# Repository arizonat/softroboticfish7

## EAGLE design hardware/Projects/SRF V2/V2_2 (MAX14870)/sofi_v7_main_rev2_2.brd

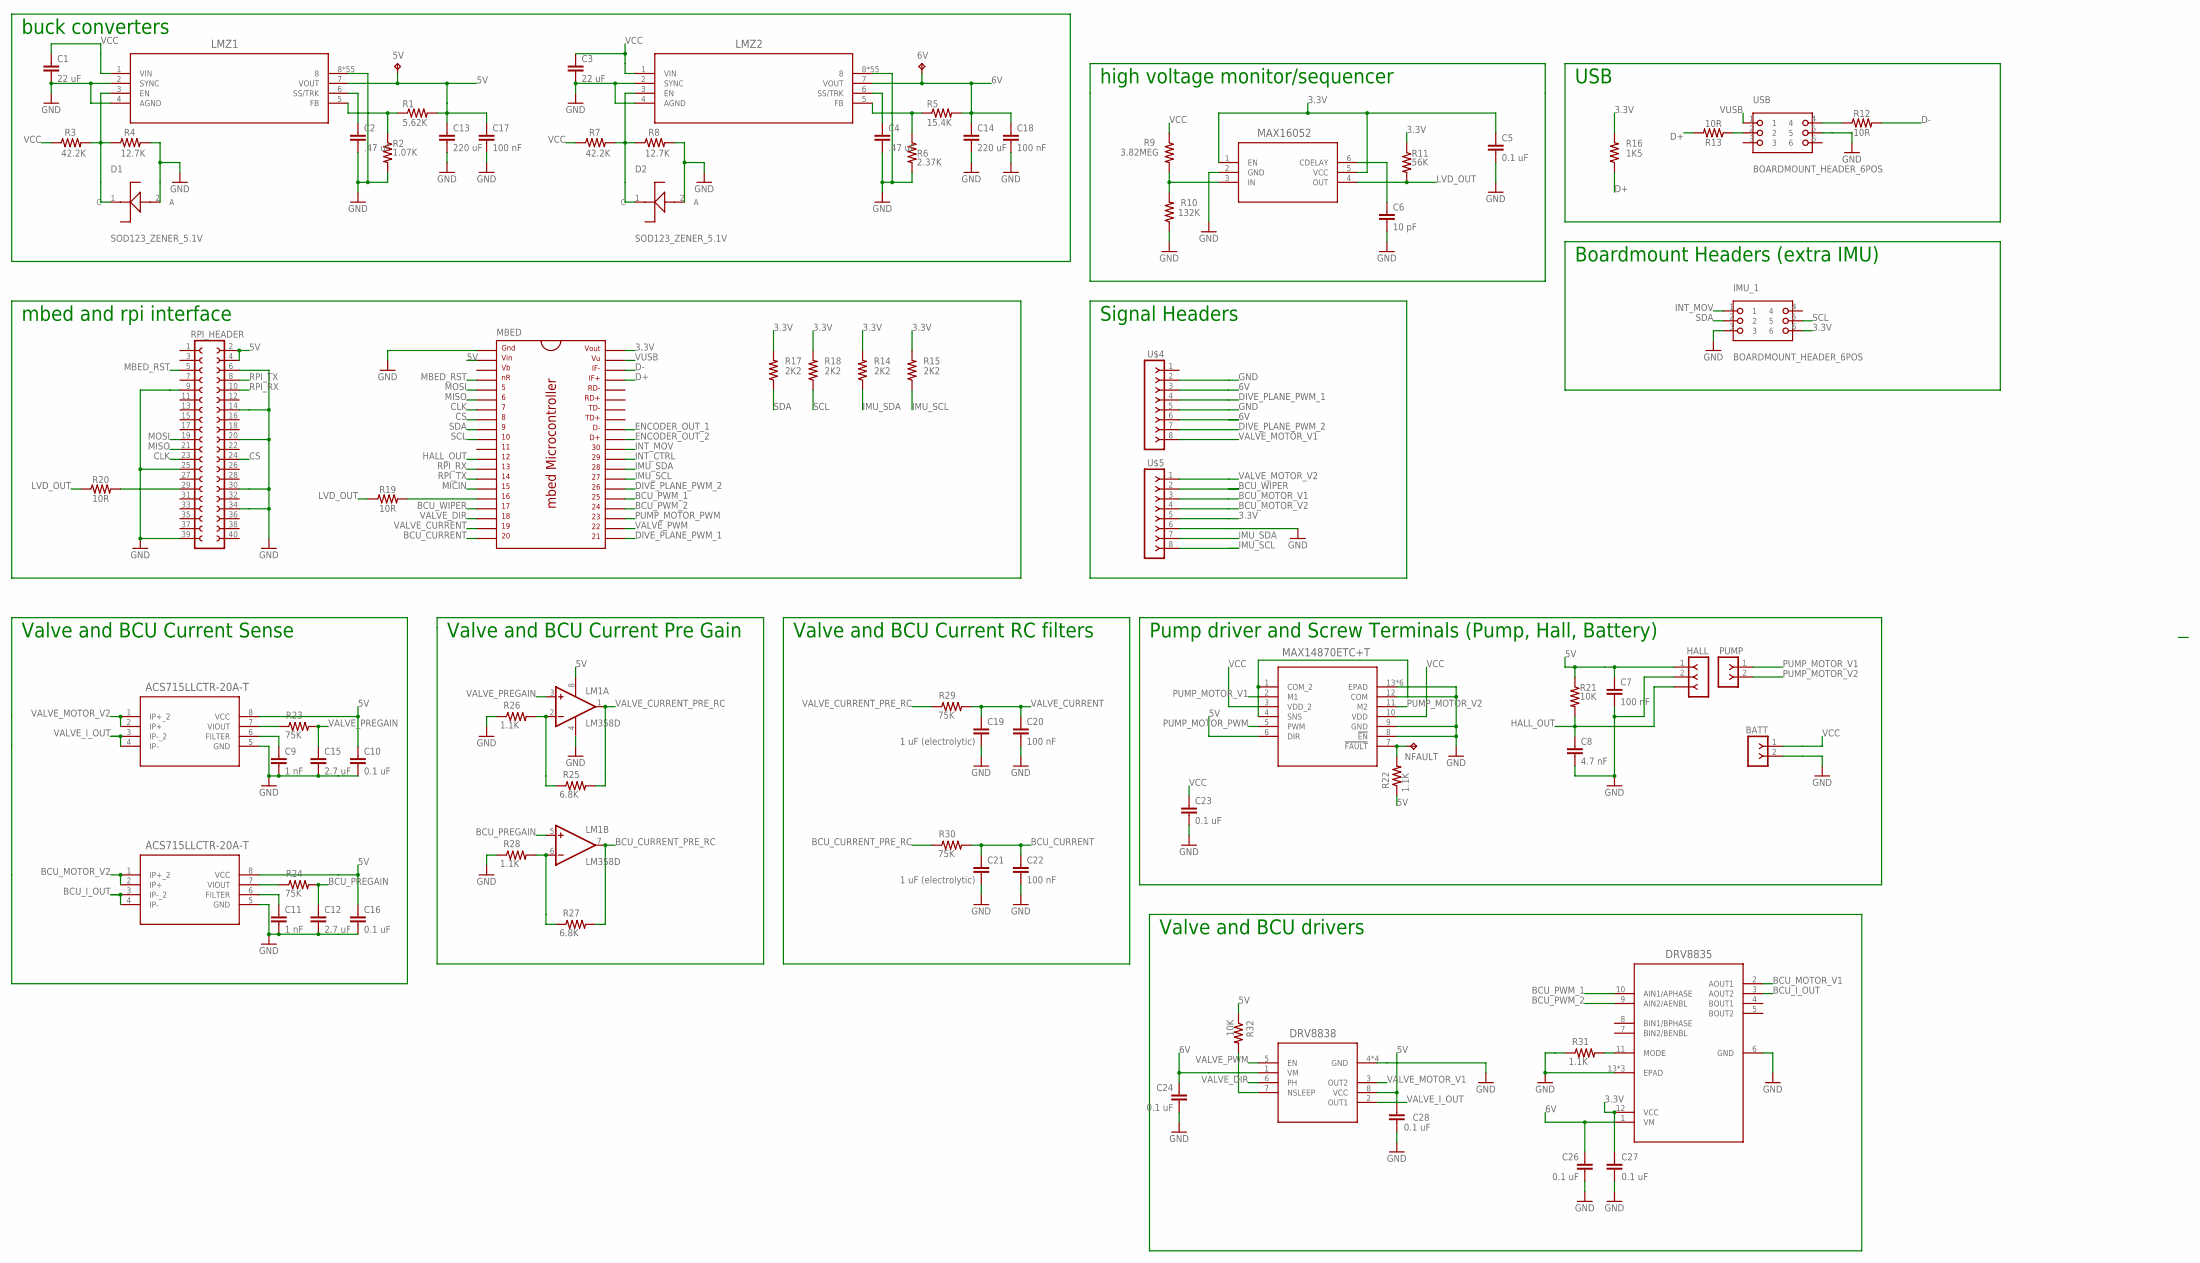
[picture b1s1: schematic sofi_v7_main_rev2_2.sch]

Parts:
5V, 6V: TPB1,27; B1,27
ACS715_BCU, ACS715_VALVE: ACS715LLCTR-20A-T; SOIC-8
BATT: 2POS_BLOCK2POS_BLOCK_NOSTANDS; 2POS_BLOCK_NOSTANDS
C1, C3: 22 uF; C0805
C2, C4: .47 uF; C0805
C5, C23: 0.1 uF; C0805
C6: 10 pF; C0603
C7, C17, C18, C20, C22: 100 nF; C0805
C8: 4.7 nF; C0805
C9, C11: 1 nF; C0603
C10, C16, C24, C26, C27, C28: 0.1 uF; C0603
C12, C15: 2.7 uF; C0603
C13, C14: 220 uF; C1206
C19, C21: 1 uF (electrolytic); C0603
D1, D2: SOD123_ZENER_5.1V; SOD123_ZENER
DRV8835: DRV8835DSSRDSS12_P9X2_THERMAL_EXTENDED; DSS12_P9X2_THERMAL_EXTENDED
DRV8838: DRV8838DSGTDSG8_P9X1P6_THERMAL_EXTENDED; DSG8_P9X1P6_THERMAL_EXTENDED
HALL: 3POS_TERMINAL
IMU_1: BOARDMOUNT_HEADER_6POS; BOARDMOUNT_HEADER
LM1: LM358D; SO08
LMZ1, LMZ2: LMZ23605TZE/NOPBTZA07A_THERMAL_TABBED; TZA07A_THERMAL_TABBED
MAX14870: MAX14870ETC+T; 21-0664B
MAX16052: MAX16052AUT+T; 21-0058I
MBED: MBED_MICROCONTROLLER; DIL40_0.9
NFAULT: TPB1,27; B1,27
PUMP: 2POS_BLOCK2POS_BLOCK_NOSTANDS; 2POS_BLOCK_NOSTANDS
R1: 5.62K; M0805
R2: 1.07K; M0805
R3, R7: 42.2K; M0805
R4, R8: 12.7K; M0805
R5: 15.4K; M0805
R6: 2.37K; M0805
R9: 3.82MEG; 0603
R10: 132K; 0603
R11: 56K; R0603
R12, R13, R19, R20: 10R; 0603
R14, R15, R17, R18: 2K2; 0603
R16: 1K5; 0603
R21, R32: 10K; M0805
R22, R26, R28, R31: 1.1K; M0805
R23, R24, R29, R30: 75K; M0805
R25, R27: 6.8K; M0805
RPI_HEADER: FE20-2
U$4, U$5: 8POS_TERMINAL
USB: BOARDMOUNT_HEADER_6POS; BOARDMOUNT_HEADER

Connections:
3.3V: C5.1, C27.1, DRV8835.12 (VCC), IMU_1.6, MAX16052.1 (EN), MAX16052.5 (VCC), MBED.40, R11.1, R14.2, R15.2, R16.2, R17.2, R18.2, U$5.5
5V: 5V.TP, ACS715_BCU.8 (VCC), ACS715_VALVE.8 (VCC), C7.1, C10.1, C13.1, C16.1, C17.1, C28.1, DRV8838.8 (VCC), HALL.1, LM1.8 (V+), LMZ1.7 (VOUT), MAX14870.6 (DIR), MBED.2, R1.2, R21.1, R22.1, R32.1, RPI_HEADER.2, RPI_HEADER.4
6V: 6V.TP, C14.1, C18.1, C24.1, C26.1, DRV8835.1 (VM), DRV8838.1 (VM), LMZ2.7 (VOUT), R5.2, U$4.3, U$4.6
BCU_CURRENT: C21.1, C22.1, MBED.20, R30.2
BCU_CURRENT_PRE_RC: LM1.7 (OUT), R27.2, R30.1
BCU_I_OUT: ACS715_BCU.3 (IP-_2), ACS715_BCU.4 (IP-), DRV8835.3 (AOUT2)
BCU_MOTOR_V1: DRV8835.2 (AOUT1), U$5.3
BCU_MOTOR_V2: ACS715_BCU.1 (IP+_2), ACS715_BCU.2 (IP+), U$5.4
BCU_PREGAIN: C12.1, LM1.5 (+IN), R24.2
BCU_PWM_1: DRV8835.10 (AIN1/APHASE), MBED.25
BCU_PWM_2: DRV8835.9 (AIN2/AENBL), MBED.24
BCU_WIPER: MBED.17, U$5.2
CLK: MBED.7, RPI_HEADER.23
CS: MBED.8, RPI_HEADER.24
D+: MBED.37, R13.2, R16.1
D-: MBED.38, R12.2
DIVE_PLANE_PWM_1: MBED.21, U$4.4
DIVE_PLANE_PWM_2: MBED.26, U$4.7
ENCODER_OUT_1: MBED.32
ENCODER_OUT_2: MBED.31
GND: ACS715_BCU.5 (GND), ACS715_VALVE.5 (GND), BATT.2, C1.2, C2.2, C3.2, C4.2, C5.2, C6.2, C7.2, C8.2, C9.2, C10.2, C11.2, C12.2, C13.2, C14.2, C15.2, C16.2, C17.2, C18.2, C19.2, C20.2, C21.2, C22.2, C23.2, C24.2, C26.2, C27.2, C28.2, D1.2 (A), D2.2 (A), DRV8835.6 (GND), DRV8835.13 (EPAD), DRV8835.P$1 (EPAD), DRV8835.P$2 (EPAD), DRV8838.4 (GND), DRV8838.9 (GND), DRV8838.P$1 (GND), DRV8838.P$2 (GND), HALL.2, IMU_1.3, LM1.4 (V-), LMZ1.2 (SYNC), LMZ1.4 (AGND), LMZ1.8, LMZ1.P$1 (8), LMZ1.P$2 (8), LMZ1.P$3 (8), LMZ1.P$4 (8), LMZ1.P$5 (8), LMZ1.P$6 (8), LMZ1.P$7 (8), LMZ1.P$8 (8), LMZ1.P$9 (8), LMZ1.P$10 (8), LMZ1.P$11 (8), LMZ1.P$12 (8), LMZ1.P$13 (8), LMZ1.P$14 (8), LMZ1.P$15 (8), LMZ1.P$16 (8), LMZ1.P$17 (8), LMZ1.P$18 (8), LMZ1.P$19 (8), LMZ1.P$20 (8), LMZ1.P$21 (8), LMZ1.P$22 (8), LMZ1.P$23 (8), LMZ1.P$24 (8), LMZ1.P$25 (8), LMZ1.P$26 (8), LMZ1.P$27 (8), LMZ1.P$28 (8), LMZ1.P$29 (8), LMZ1.P$30 (8), LMZ1.P$31 (8), LMZ1.P$32 (8), LMZ1.P$33 (8), LMZ1.P$34 (8), LMZ1.P$35 (8), LMZ1.P$36 (8), LMZ1.P$37 (8), LMZ1.P$38 (8), LMZ1.P$39 (8), LMZ1.P$40 (8), LMZ1.P$41 (8), LMZ1.P$42 (8), LMZ1.P$43 (8), LMZ1.P$44 (8), LMZ1.P$45 (8), LMZ1.P$46 (8), LMZ1.P$47 (8), LMZ1.P$48 (8), LMZ1.P$49 (8), LMZ1.P$50 (8), LMZ1.P$51 (8), LMZ1.P$52 (8), LMZ1.P$53 (8), LMZ1.P$54 (8), LMZ2.2 (SYNC), LMZ2.4 (AGND), LMZ2.8, LMZ2.P$1 (8), LMZ2.P$2 (8), LMZ2.P$3 (8), LMZ2.P$4 (8), LMZ2.P$5 (8), LMZ2.P$6 (8), LMZ2.P$7 (8), LMZ2.P$8 (8), LMZ2.P$9 (8), LMZ2.P$10 (8), LMZ2.P$11 (8), LMZ2.P$12 (8), LMZ2.P$13 (8), LMZ2.P$14 (8), LMZ2.P$15 (8), LMZ2.P$16 (8), LMZ2.P$17 (8), LMZ2.P$18 (8), LMZ2.P$19 (8), LMZ2.P$20 (8), LMZ2.P$21 (8), LMZ2.P$22 (8), LMZ2.P$23 (8), LMZ2.P$24 (8), LMZ2.P$25 (8), LMZ2.P$26 (8), LMZ2.P$27 (8), LMZ2.P$28 (8), LMZ2.P$29 (8), LMZ2.P$30 (8), LMZ2.P$31 (8), LMZ2.P$32 (8), LMZ2.P$33 (8), LMZ2.P$34 (8), LMZ2.P$35 (8), LMZ2.P$36 (8), LMZ2.P$37 (8), LMZ2.P$38 (8), LMZ2.P$39 (8), LMZ2.P$40 (8), LMZ2.P$41 (8), LMZ2.P$42 (8), LMZ2.P$43 (8), LMZ2.P$44 (8), LMZ2.P$45 (8), LMZ2.P$46 (8), LMZ2.P$47 (8), LMZ2.P$48 (8), LMZ2.P$49 (8), LMZ2.P$50 (8), LMZ2.P$51 (8), LMZ2.P$52 (8), LMZ2.P$53 (8), LMZ2.P$54 (8), MAX14870.1 (COM_2), MAX14870.4 (SNS), MAX14870.8 (!EN), MAX14870.9 (GND), MAX14870.12 (COM), MAX14870.13 (EPAD), MAX14870.14 (EPAD), MAX14870.15 (EPAD), MAX14870.16 (EPAD), MAX14870.17 (EPAD), MAX14870.18 (EPAD), MAX16052.2 (GND), MBED.1, R2.2, R4.2, R6.2, R8.2, R10.1, R26.1, R28.1, R31.1, RPI_HEADER.6, RPI_HEADER.9, RPI_HEADER.14, RPI_HEADER.20, RPI_HEADER.25, RPI_HEADER.30, RPI_HEADER.34, RPI_HEADER.39, U$4.2, U$4.5, U$5.6, USB.5
HALL_OUT: C8.1, HALL.3, MBED.12, R21.2
IMU_SCL: MBED.27, R15.1, U$5.8
IMU_SDA: MBED.28, R14.1, U$5.7
INT_CTRL: MBED.29
INT_MOV: IMU_1.1, MBED.30
LVD_OUT: MAX16052.4 (OUT), R11.2, R19.1, R20.1
MBED_RST: MBED.4, RPI_HEADER.5
MICIN: MBED.15
MISO: MBED.6, RPI_HEADER.21
MOSI: MBED.5, RPI_HEADER.19
unnamed: R20.2, RPI_HEADER.29
unnamed: MAX14870.7 (!FAULT), NFAULT.TP, R22.2
unnamed: LMZ1.5 (FB), R1.1, R2.1
unnamed: MAX16052.3 (IN), R9.2, R10.2
unnamed: D1.1 (C), LMZ1.3 (EN), R3.2, R4.1
unnamed: C4.1, LMZ2.6 (SS/TRK)
unnamed: LMZ2.5 (FB), R5.1, R6.1
unnamed: C2.1, LMZ1.6 (SS/TRK)
unnamed: C6.1, MAX16052.6 (CDELAY)
unnamed: D2.1 (C), LMZ2.3 (EN), R7.2, R8.1
unnamed: ACS715_VALVE.7 (VIOUT), R23.1
unnamed: ACS715_VALVE.6 (FILTER), C9.1
unnamed: MBED.16, R19.2
unnamed: ACS715_BCU.7 (VIOUT), R24.1
unnamed: ACS715_BCU.6 (FILTER), C11.1
unnamed: LM1.2 (-IN), R25.1, R26.2
unnamed: R12.1, USB.4
unnamed: LM1.6 (-IN), R27.1, R28.2
unnamed: R13.1, USB.2
unnamed: DRV8835.11 (MODE), R31.2
unnamed: DRV8838.7 (NSLEEP), R32.2
PUMP_MOTOR_PWM: MAX14870.5 (PWM), MBED.23
PUMP_MOTOR_V1: MAX14870.2 (M1), PUMP.1
PUMP_MOTOR_V2: MAX14870.11 (M2), PUMP.2
RPI_RX: MBED.13, RPI_HEADER.10
RPI_TX: MBED.14, RPI_HEADER.8
SCL: IMU_1.5, MBED.10, R18.1
SDA: IMU_1.2, MBED.9, R17.1
VALVE_CURRENT: C19.1, C20.1, MBED.19, R29.2
VALVE_CURRENT_PRE_RC: LM1.1 (OUT), R25.2, R29.1
VALVE_DIR: DRV8838.6 (PH), MBED.18
VALVE_I_OUT: ACS715_VALVE.3 (IP-_2), ACS715_VALVE.4 (IP-), DRV8838.2 (OUT1)
VALVE_MOTOR_V1: DRV8838.3 (OUT2), U$4.8
VALVE_MOTOR_V2: ACS715_VALVE.1 (IP+_2), ACS715_VALVE.2 (IP+), U$5.1
VALVE_PREGAIN: C15.1, LM1.3 (+IN), R23.2
VALVE_PWM: DRV8838.5 (EN), MBED.22
VCC: BATT.1, C1.1, C3.1, C23.1, LMZ1.1 (VIN), LMZ2.1 (VIN), MAX14870.3 (VDD_2), MAX14870.10 (VDD), R3.1, R7.1, R9.1
VUSB: MBED.39, USB.1

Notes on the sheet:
mbed and rpi interface
buck converters
high voltage monitor/sequencer
Valve and BCU Current RC filters
Valve and BCU Current Pre Gain
Valve and BCU Current Sense
Signal Headers
USB
Pump driver and Screw Terminals (Pump, Hall, Battery)
Valve and BCU drivers
Boardmount Headers (extra IMU)

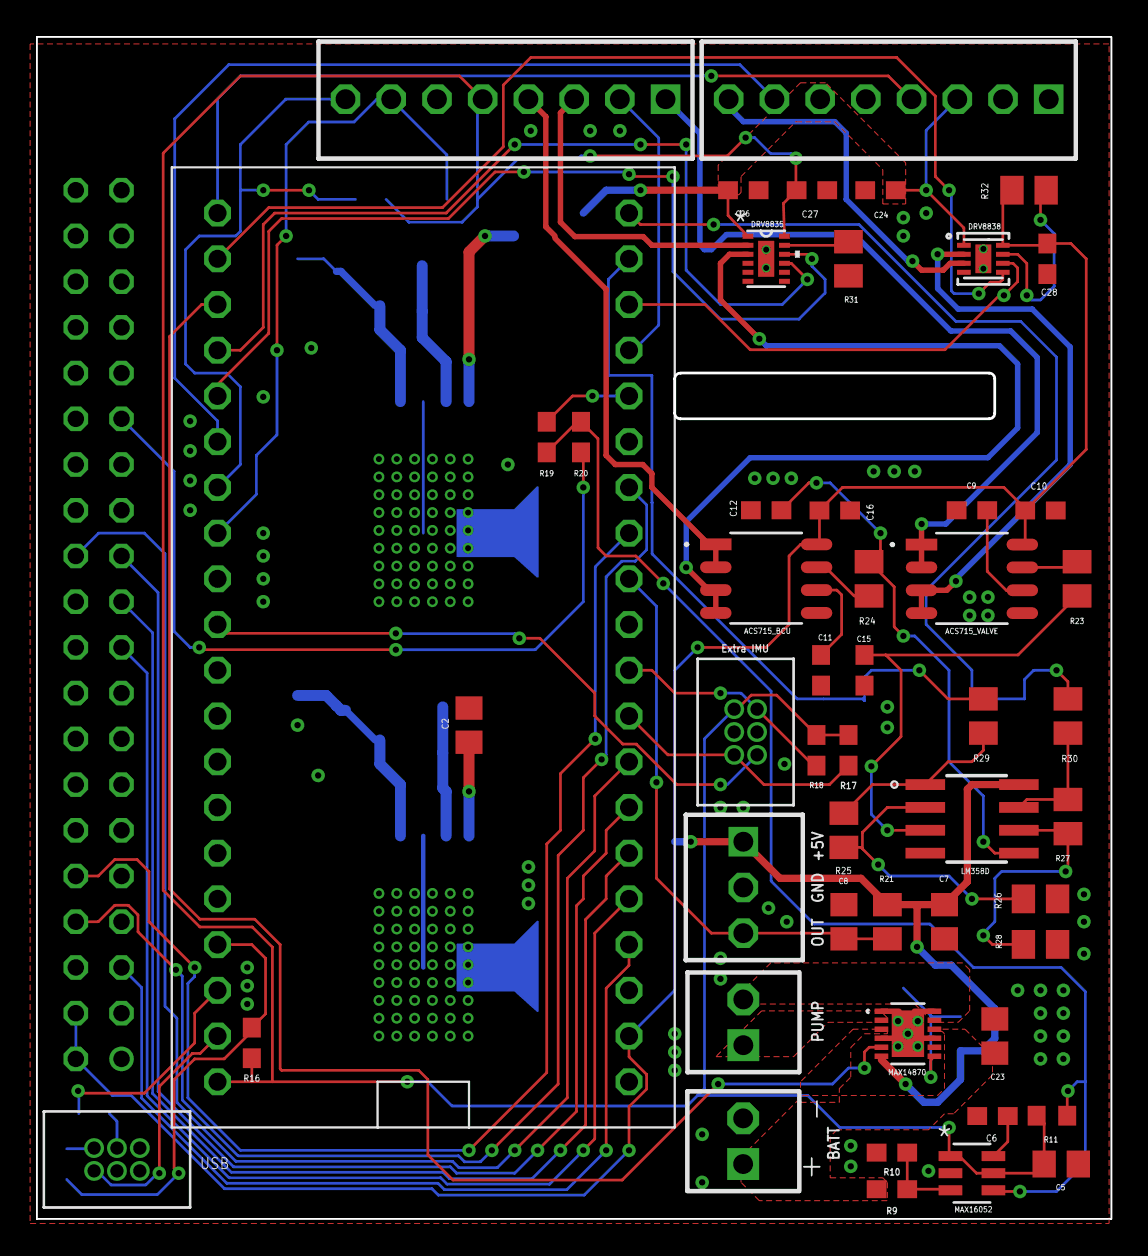
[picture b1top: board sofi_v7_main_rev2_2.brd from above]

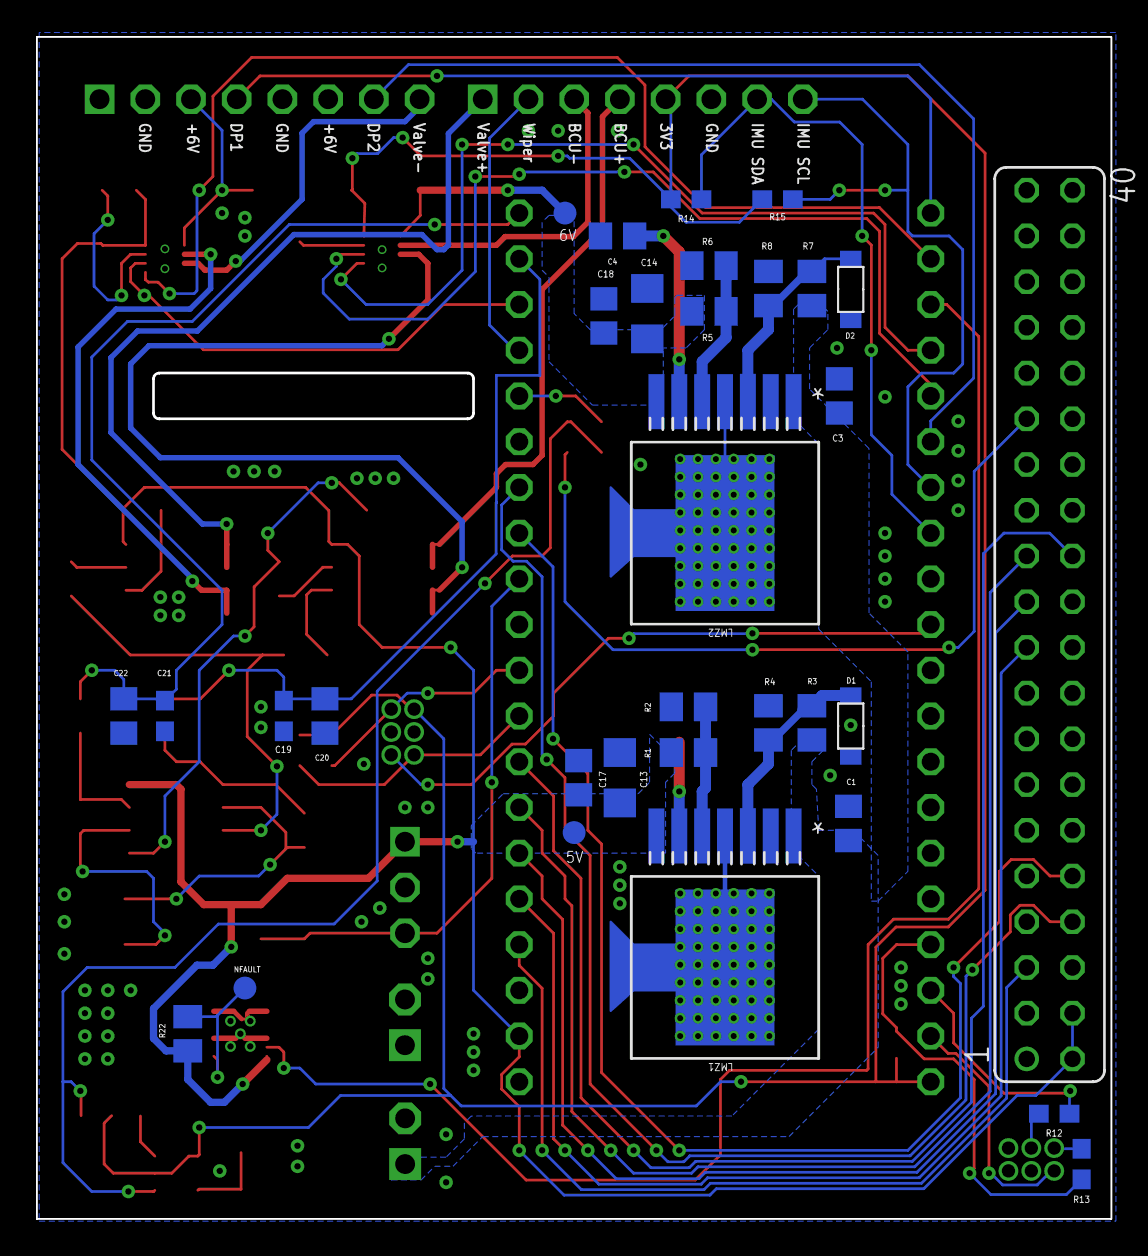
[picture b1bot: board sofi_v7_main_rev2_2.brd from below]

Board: 2 copper layers, 59.7 x 65.7 mm, 82 parts (32 on the bottom side), 65 nets.

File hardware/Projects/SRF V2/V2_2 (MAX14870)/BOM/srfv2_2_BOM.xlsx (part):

Manufacturer Part Number | Manufacturer | Digi-Key Part Number | Customer Reference | Reference Designator | Packaging | Part Status | Quantity | Unit Price | Extended Price | Quantity Available | Mfg Std Lead Time | Description | RoHS Status | Lead Free Status | REACH Status
ACS715LLCTR-20A-T | Allegro MicroSystems | 620-1230-1-ND |  | ACS715_BCU, ACS715_VALVE | Cut Tape (CT) | Not For New Designs | 2.0 | 6.52 | $13.04 | 3330.0 | Not Available | SENSOR CURRENT HALL 20A DC | ROHS3 Compliant | Contains lead | REACH Unaffected
45206-600230 | 3M | 3M15533-ND |  | USB | Tray | Active | 2.0 | 2.1 | $4.20 | 570.0 | 10 Weeks | CONN HEADER VERT 6POS 1.27MM | ROHS3 Compliant | Lead free | Not Available
DRV8835DSSR | Texas Instruments | 296-30391-2-ND |  | DRV8835 | Tape & Reel (TR) | Active | 1.0 | 0.0 | $0.00 | 21000.0 | 6 Weeks | IC MTR DRVR BIPOLAR 2-7V 12WSON | ROHS3 Compliant | Lead free | REACH Unaffected
DRV8838DSGT | Texas Instruments | 296-37539-1-ND |  | DRV8838 | Cut Tape (CT) | Active | 1.0 | 1.03 | $1.03 | 3356.0 | 6 Weeks | IC BRIDGE DRIVER PAR 8WSON | ROHS3 Compliant | Lead free | REACH Unaffected
1725656.0 | Phoenix Contact | 277-1273-ND |  | BATT, PUMP | Bulk | Active | 2.0 | 1.41 | $2.82 | 7140.0 | 7 Weeks | TERM BLK 2P SIDE ENT 2.54MM PCB | RoHS Compliant | Lead free | Not Available
MAX14870ETC+T | Maxim Integrated | MAX14870ETC+CT-ND |  | MAX14870 | Cut Tape (CT) | Active | 1.0 | 2.51 | $2.51 | 10600.0 | 7 Weeks | IC MOTOR DRIVER 4.5V-36V 12TDFN | ROHS3 Compliant | Lead free | REACH Unaffected
MAX16052AUT+T | Maxim Integrated | MAX16052AUT+TCT-ND |  | MAX16052 | Cut Tape (CT) | Active | 1.0 | 2.27 | $2.27 | 15019.0 | 6 Weeks | IC PWR MONITOR/SEQUENCER SOT23-6 | ROHS3 Compliant | Lead free | REACH Unaffected
PPPC202LFBN-RC | Sullins Connector Solutions | S7123-ND |  | RPI_HEADER | Tray | Active | 1.0 | 2.03 | $2.03 | 4207.0 | 5 Weeks | CONN HDR 40POS 0.1 GOLD PCB | ROHS3 Compliant | Lead free | REACH Unaffected
OM11043,598 | NXP USA Inc. | 568-4916-ND |  | MBED | Box | Active | 1.0 | 52.06 | $52.06 | 0.0 | 12 Weeks | MBED LPC176X DEV EVAL BRD | ROHS3 Compliant | Lead free | REACH Unaffected
OSTVN08A150 | On Shore Technology Inc. | ED10566-ND |  | U$4, U$5 | Bulk | Active | 2.0 | 2.01 | $4.02 | 2383.0 | 8 Weeks | TERM BLK 8P SIDE ENT 2.54MM PCB | ROHS3 Compliant | Lead free | REACH Unaffected
OSTVN03A150 | On Shore Technology Inc. | ED10562-ND |  | HALL | Bulk | Active | 1.0 | 0.88 | $0.88 | 12192.0 | 8 Weeks | TERM BLK 3P SIDE ENT 2.54MM PCB | ROHS3 Compliant | Lead free | REACH Unaffected
MMSZ4689-TP | Micro Commercial Co | MMSZ4689-TPMSCT-ND |  | D1, D2 | Cut Tape (CT) | Active | 2.0 | 0.17 | $0.34 | 41011.0 | 12 Weeks | DIODE ZENER 5.1V 500MW SOD123 | ROHS3 Compliant | Lead free | REACH Unaffected
LMZ23605TZE/NOPB | Texas Instruments | 296-35357-1-ND |  | LMZ1, LMZ2 | Cut Tape (CT) | Active | 2.0 | 11.76 | $23.52 | 3608.0 | 6 Weeks | DC DC CONVERTER 0.8-6V 5A | ROHS3 Compliant | Lead free | REACH Unaffected
LM358DT | STMicroelectronics | 497-1591-1-ND |  | LM1 | Cut Tape (CT) | Active | 1.0 | 0.4 | $0.40 | 95056.0 | 6 Weeks | IC OPAMP GP 2 CIRCUIT 8SO | ROHS3 Compliant | Lead free | REACH Unaffected
GRT21BR61E226ME13L | Murata Electronics | 490-12389-1-ND |  | C1, C3 | Cut Tape (CT) | Active | 2.0 | 0.54 | $1.08 | 208357.0 | 19 Weeks | CAP CER 22UF 25V X5R 0805 | ROHS3 Compliant | Lead free | Not Available
GRM31CR60J227ME11L | Murata Electronics | 490-13970-1-ND |  | C13, C14 | Cut Tape (CT) | Active | 2.0 | 1.42 | $2.84 | 169292.0 | 15 Weeks | CAP CER 220UF 6.3V X5R 1206 | ROHS3 Compliant | Lead free | Not Available
C0805C104K9RACTU | KEMET | 399-9155-1-ND |  | C17, C18 | Cut Tape (CT) | Active | 2.0 | 0.21 | $0.42 | 70826.0 | 8 Weeks | CAP CER 0.1UF 6.3V X7R 0805 | ROHS3 Compliant | Lead free | REACH Unaffected
TACL105K006RTA | AVX Corporation | 478-8774-1-ND |  | C19, C21 | Cut Tape (CT) | Active | 2.0 | 2.16 | $4.32 | 0.0 | 23 Weeks | CAP TANT 1UF 10% 6.3V 0603 | ROHS3 Compliant | Lead free | REACH Unaffected
C2012X7R1V474K125AB | TDK Corporation | 445-14549-1-ND |  | C2, C4 | Cut Tape (CT) | Not For New Designs | 2.0 | 0.27 | $0.54 | 416.0 | Not Available | CAP CER 0.47UF 35V X7R 0805 | ROHS3 Compliant | Lead free | REACH Unaffected
LD055C104JAB2A | AVX Corporation | 478-10963-1-ND |  | C20, C22, C7 | Cut Tape (CT) | Active | 3.0 | 0.65 | $1.95 | 24151.0 | 24 Weeks | CAP CER 0.1UF 50V X7R 0805 | RoHS non-compliant | Contains lead | REACH Unaffected
CL21F104ZBCNNNC | Samsung Electro-Mechanics | 1276-1007-1-ND |  | C5, C23 | Cut Tape (CT) | Active | 2.0 | 0.09 | $0.18 | 608050.0 | 22 Weeks | CAP CER 0.1UF 50V Y5V 0805 | ROHS3 Compliant | Lead free | REACH Unaffected
CL10C100JB8NFNC | Samsung Electro-Mechanics | 1276-2155-2-ND |  | C6 | Tape & Reel (TR) | Active | 1.0 | 0.0 | $0.00 | 84000.0 | 18 Weeks | CAP CER 10PF 50V C0G/NP0 0603 | ROHS3 Compliant | Lead free | REACH Unaffected
C0603C102J5GALTU | KEMET | 399-6346-1-ND |  | C9, C11 | Cut Tape (CT) | Active | 2.0 | 0.39 | $0.78 | 7653.0 | 29 Weeks | CAP CER 1000PF 50V C0G/NP0 0603 | RoHS non-compliant | Contains lead | REACH Unaffected
GCM188R71H104KA57J | Murata Electronics | 490-8020-1-ND |  | C10,C12, C16, C24, C26, C27, C28 | Cut Tape (CT) | Not For New Designs | 7.0 | 0.23 | $1.61 | 956922.0 | Not Available | CAP CER 0.1UF 50V X7R 0603 | ROHS3 Compliant | Lead free | Not Available
GRM188R61H225KE11D | Murata Electronics | 490-10733-1-ND |  | C12, C15 | Cut Tape (CT) | Active | 2.0 | 0.29 | $0.58 | 182633.0 | 15 Weeks | CAP CER 2.2UF 50V X5R 0603 | ROHS3 Compliant | Lead free | Not Available
VJ0805Y472KXACW1BC | Vishay Vitramon | 720-1605-1-ND |  | C8 | Cut Tape (CT) | Active | 1.0 | 0.25 | $0.25 | 92564.0 | 14 Weeks | CAP CER 4700PF 50V X7R 0805 | ROHS3 Compliant | Lead free | Not Available
ERJ-6ENF5621V | Panasonic Electronic Components | P5.62KCCT-ND |  | R1 | Cut Tape (CT) | Active | 1.0 | 0.09 | $0.09 | 23833.0 | 16 Weeks | RES SMD 5.62K OHM 1% 1/8W 0805 | ROHS3 Compliant | Lead free | REACH Unaffected
MCR03ERTJ563 | Rohm Semiconductor | RHM56KCGCT-ND |  | R11 | Cut Tape (CT) | Discontinued at Digi-Key | 1.0 | 0.09 | $0.09 | 766.0 | Not Available | RES SMD 56K OHM 5% 1/10W 0603 | ROHS3 Compliant | Lead free | REACH Unaffected
RC1608J152CS | Samsung Electro-Mechanics | 1276-5066-1-ND |  | R16 | Cut Tape (CT) | Discontinued at Digi-Key | 1.0 | 0.09 | $0.09 | 3780.0 | Not Available | RES SMD 1.5K OHM 5% 1/10W 0603 | ROHS3 Compliant | Lead free | REACH Unaffected
RC1608F330CS | Samsung Electro-Mechanics | 1276-4524-1-ND |  | R12, R13 | Cut Tape (CT) | Discontinued at Digi-Key | 2.0 | 0.09 | $0.18 | 153.0 | Not Available | RES SMD 33 OHM 1% 1/10W 0603 | ROHS3 Compliant | Lead free | REACH Unaffected
KTR03EZPF10R0 | Rohm Semiconductor | RHM10.0AYCT-ND |  | R19, R20 | Cut Tape (CT) | Active | 2.0 | 0.12 | $0.24 | 2215.0 | 10 Weeks | RES SMD 10 OHM 1% 1/10W 0603 | ROHS3 Compliant | Lead free | REACH Unaffected
ERJ-6ENF1071V | Panasonic Electronic Components | P1.07KCCT-ND |  | R2 | Cut Tape (CT) | Active | 1.0 | 0.09 | $0.09 | 35297.0 | 16 Weeks | RES SMD 1.07K OHM 1% 1/8W 0805 | ROHS3 Compliant | Lead free | REACH Unaffected
CRS0805-FX-1002ELF | Bourns Inc. | CRS0805-FX-1002ELFCT-ND |  | R21, R32 | Cut Tape (CT) | Active | 2.0 | 0.32 | $0.64 | 6554.0 | 16 Weeks | RES SMD 10K OHM 1% 1/4W 0805 | ROHS3 Compliant | Lead free | REACH Unaffected
ERJ-6ENF7502V | Panasonic Electronic Components | P75.0KCCT-ND |  | R29, R30, R24, R23 | Cut Tape (CT) | Active | 4.0 | 0.09 | $0.36 | 62375.0 | 16 Weeks | RES SMD 75K OHM 1% 1/8W 0805 | ROHS3 Compliant | Lead free | REACH Unaffected
ERA-6AEB4222V | Panasonic Electronic Components | P42.2KDACT-ND |  | R3, R7 | Cut Tape (CT) | Active | 2.0 | 0.29 | $0.58 | 11630.0 | 12 Weeks | RES 42.2K OHM 0.1% 1/8W 0805 | ROHS3 Compliant | Lead free | REACH Unaffected
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
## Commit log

2020-06-02 added EAGLE CAD libraries for SoFi board parts
2020-06-12 added board files and libraries
2020-06-15 added GND plane vias to minimize current return paths, modified 2POS_BLOCK lib
2020-06-15 generated new CAM files
2020-06-19 Removed the old ros directory contents and an accidental raspicam_node commit
2020-06-19 Removing more old code
2020-06-19 Removed more old files and added the submodule for raspicam_node
2020-06-22 new motor driver footprints with extended pads, thermals test
2020-06-22 cleaning some unstaged changes w/ BufferedSerial
2020-06-22 Removing more old files
2020-06-22 "Made AutoController Node take camera images"
2020-06-22 added power planes for VCC to power modules, pump motor outputs
2020-06-23 Incorporate ROS images into the fish state controller
2020-06-23 extended motor driver pads, removed top thermals on power module thermal vias
2020-06-23 "Mask from image processing is now published"
2020-06-23 changed serial port to /dev/serial0 on bluetooth joy
2020-06-24 defined corner radius around camera cable cut-out, widened valve & bcu motor output traces for safety, rearranged some polygons
2020-06-24 generated PCBWay gerbers, pick & place, saved BOM
2020-06-24 added a fish state publisher to the Autocontroller
2020-06-25 regenerated CAM outputs due to submission failure
2020-06-25 testing mbed->pi serial
2020-06-25 mbed->pi USB serial works, port=/dev/ttyACM0
2020-06-25 mbed -> pi wired serial works in log_serial_test.py, REMOVE ANY CONSOLE PARTS FROM /boot/cmdline.txt THAT RELATES TO SERIAL0
2020-06-26 Custom message implemented into Autocontroller
2020-06-26 HSV settings reset
2020-06-26 more experimentation w/ serial, now sending fish states mbed -> pi
2020-06-26 fixed PCBWay drill size issue, removed thermals on LMZ pad for future revision, generated final CAM files
2020-06-29 mbed code cleanup on MCUXpresso
2020-06-29 git cleanup
2020-06-29 more cleanup
2020-06-30 retesting autoMode
2020-07-03 "Source files added"
2020-07-03 Added distance and offset tracking to the fish state controller
2020-07-03 fixed errors in state message publishing
2020-07-08 "Minor code cleanup and message gen for fish pos"
2020-07-08 "Pose stuff added"
2020-07-08 added TestController for testing/debugging purposes
2020-07-09 fixed minor error in NaiveColorTargetTracker.process_image; uncommented mbed code
2020-07-09 sign flip on the horizontal (y) offset
2020-07-10 added PITCH_UP and PITCH_DOWN commands
2020-07-10 changed to default mode (no auto mode, infinite serial loop, no debug printing)
2020-07-13 set Vfreq scale term to 450000 instead 0f 400000
2020-07-14 "Autocontroller file adjusted"
2020-07-15 "Slight correction to speed adjust block"
2020-07-15 "Removed devel file"
2020-07-15 updated test controller to accept command inputs in loop
2020-07-15 changed serial terminating byte from 8 to 0 for 1-255 ranges
2020-07-15 changed max frequency from 1.6 Hz to 1.2 Hz, changed serial input range to 1-255, changed terminating byte from 8 to 0 for new ranges, added new valve control debug helper functions
2020-07-17 added PCBWay issue resolution snapshots
2020-07-30 updated IMU_Test to include correct library
2020-07-31 "Adjusted used blocks in autocontroller file"
2020-08-03 modified BCU and FishController for imu initialization setup
2020-08-04 added serial node package
2020-08-05 "Purple color tracker. Added new fish state. "
2020-08-05 "Added new fish state. Minor changes for code run"
2020-08-07 "Now allows for control of motor on state"
2020-08-11 "Slightly more fine tuned controls"
2020-08-11 modified IMU test, added Vfreq constraint in PumpWithValve
2020-08-11 changed usbSerial to serial for wired UART
2020-08-11 added separate node for object tracking/state estimation
2020-08-12 started imu parsing
2020-08-12 updated serial_node.py
2020-08-12 "Wait function ifdef"
2020-08-13 added custom serial reading for IMU measurements in log_serial_test.py and serial_node.py
2020-08-13 fixed length of outgoing IMU data string in test script
2020-08-13 publishing to target_found topic from ObjectTracker
2020-08-13 serial_node now parses imu data into Imu messages and publishes
2020-08-14 "First draft config files just for colors"
2020-08-14 added IMU compass heading measurements in serial_node.py, reverted log_serial_test back to old state, buffer serial now in log_imu_test.py
2020-08-14 now sending pitch, roll, yaw, heading from IMU_Test
2020-08-17 Performed and recorded manual testing for the ObjectTracker; fixed minor errors
2020-08-17 Changed tracker rate to 24hz (about as fast as it can go)
2020-08-18 "Pause start implemented"
2020-08-20 First implementation of Finite State Machine node for SoFi
2020-08-20 Fixed small errors after testing the FishStateMachine and recorded manual testing notes
2020-08-20 Created pid controller launch file
2020-08-21 Fixed bug occuring in ObjectTracker that would prevent the heading average from being calculated
2020-08-25 changed imu topic to /imu/data, corrected IMU message publishing
2020-08-25 added new data elements into fixed string
2020-08-25 Created Serial node for fishstatecontroller
2020-08-26 creating src directory for fishstatecontroller package
2020-08-27 "Pause Start reimplimented"
2020-08-31 Added pitch and distance feedback to PID controller and serial node
2020-08-31 Added pitch and distance feedback to ObjectTracker and FishStateMachine; minor fies in auto_controller.launch and serial node
2020-09-01 fixed degrees -> rad conversion for euler angles
2020-09-03 Changed scale of pid controller output from -10/+10 to -1/+1; minor bug fix in serial node
2020-09-10 updated IMU test code
2020-09-11 added robot_localization reference folder (not a ROS package)
2020-09-14 added preliminary instructions for setting up robot_localization on your pi
2020-09-29 Fixed SEARCH state pattern
2020-10-07 added custom raspicam launch & param files for 640x410 resolution
2020-10-07 added ObjectTracker for 410x308 resolution
2020-10-17 Added README file to the fishstatecontroller directory
2020-10-17 modified README in the fishstatecontroller directory
2020-10-17 created launch file to start all SoFi nodes
2020-10-19 modified IMU test script, reverted fish valve parameters to original
2020-10-19 added calibration_parser file, which parses and stores camera info
2020-10-19 new mode for sofi.launch file
2020-10-21 created new ObjectTracker_fusion.py for IMU + Camera fusion, wrote new TODOs and ROS pub/subs
2020-10-22 almost done w/ pubs, need to convert imu to twist
2020-10-22 added serial_node_fusion.py, modified ObjectTracker_fusion.py
2020-10-23 first pass imu + cam implemented, saved robot_localization files
2020-10-23 added Imu pub in ObjectTracker_fusion.py
2020-10-23 ekf_imu_cam.yaml now configures imu, twist, and pose
2020-10-27 Created new raspicam_node resolution and calibration files
2020-11-07 saved test configuration
2020-11-07 cleaned up FISH4 code for easy toggling
2020-11-15 added ObjectTracker_320x240.py
2020-11-16 State Controller current stage
2020-11-24 Added a tool for selecting HSV colors
2020-12-03 added new calibration file, removed subsampling from Object Tracker, implemted object tracking with header angle
2020-12-04 Created Blob Tracker
2020-12-08 added IMU class
2020-12-08 updated IMU class
2020-12-09 modified IMU class
2020-12-10 added extra IMU helper functions
2020-12-17 Implemented area and color filter for blob tracker
2020-12-18 Added filtering to remove mirrored surface objects and fuzzy objects
2020-12-22 tate Machine stuff added
2021-01-15 Created Manual Control File
2021-01-19 created launch file with auto and manual control
2021-01-19 minor changes to decrease delay in manual controller commands
2021-01-21 Fixed minor changes in manual controller and serial node; began writing visualization code
2021-01-27 added IMU data writes (ifdef) in SerialController
2021-01-29 Update BlobTracker_320x240.py
    Fixed an issue with over filtering of targets
2021-01-29 Added visualization stuff and pictures of graphs from bagfiles
2021-01-29 Implemented more frequent heading averaging and smarter search state
2021-02-03 minor change to sofi.launch file, added graphs of 2_2_21 bagfiles
2021-02-08 added picam params yaml
2021-02-11 modified FishStateMachine.py to set no search direction at startup
2021-02-19 Made sofi_dashboard compatible with python3/noetic
2021-02-22 set pitch and thrust control to be off by default; added camera parameters
2021-02-26 Simple average heading experiments
2021-02-27 Added window based averaging as well
2021-02-28 Added a few more experiments for heading averaging, including what the ROS PID filter does maybe, though maybe not since it needs to operate on the derivative
2021-02-28 Implemented Braden filter for comparison
2021-03-05 implemented hack to filter fish head oscillations in PID node
2021-03-05 Added a fixed sample rate of Bradens filter and better print statements
2021-03-12 Added a heading setpoint to the launch faile
2021-03-12 implemented low pass filter on state estimation
2021-03-16 added graphs to show the performance of the implemented lpf
2021-03-19 Made the controller more robust against temporary loss of target position
2021-03-19 minor fixes
2021-04-30 adding gazebo model of nose cone
2021-06-10 removed button interrupt code to resolve serial command delay issues

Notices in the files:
parts and their libraries:
SparkFun-Resistors: Licensing: Creative Commons ShareAlike 4.0 International - https://creativecommons.org/licenses/by-sa/4.0
COPYRIGHT: Copyright (C) 2018 Accelerated Designs. All rights reserved
